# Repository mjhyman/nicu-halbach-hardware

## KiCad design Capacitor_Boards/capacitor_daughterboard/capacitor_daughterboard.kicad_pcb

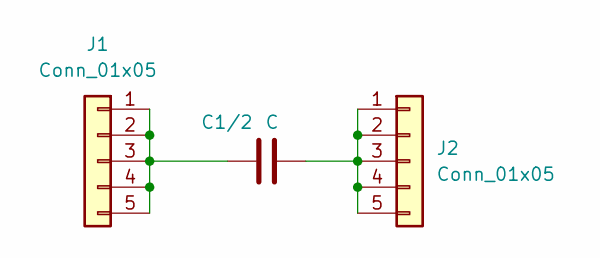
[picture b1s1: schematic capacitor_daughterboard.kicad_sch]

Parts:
C1/2: C; C_2225_5664Metric_Pad1.80x6.60mm_HandSolder
J1, J2: Conn_01x05; PinHeader_1x05_P2.54mm_Vertical

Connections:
unnamed: C1/2.1, J1.1, J1.2, J1.3, J1.4, J1.5
unnamed: C1/2.2, J2.1, J2.2, J2.3, J2.4, J2.5

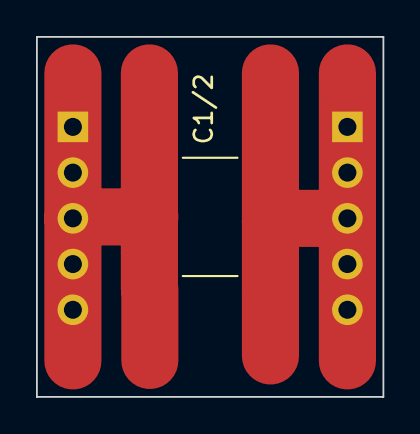
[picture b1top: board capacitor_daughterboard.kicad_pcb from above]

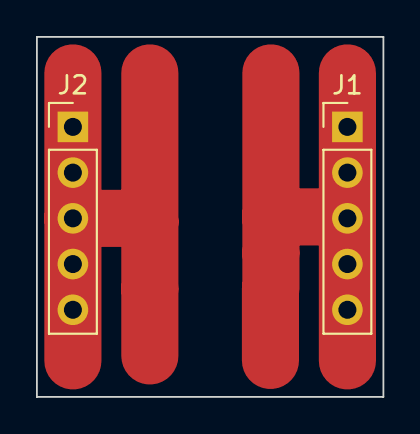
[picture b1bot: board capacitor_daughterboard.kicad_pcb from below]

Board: 2 copper layers, 19.2 x 20.0 mm, 3 parts (2 on the bottom side), 2 nets.

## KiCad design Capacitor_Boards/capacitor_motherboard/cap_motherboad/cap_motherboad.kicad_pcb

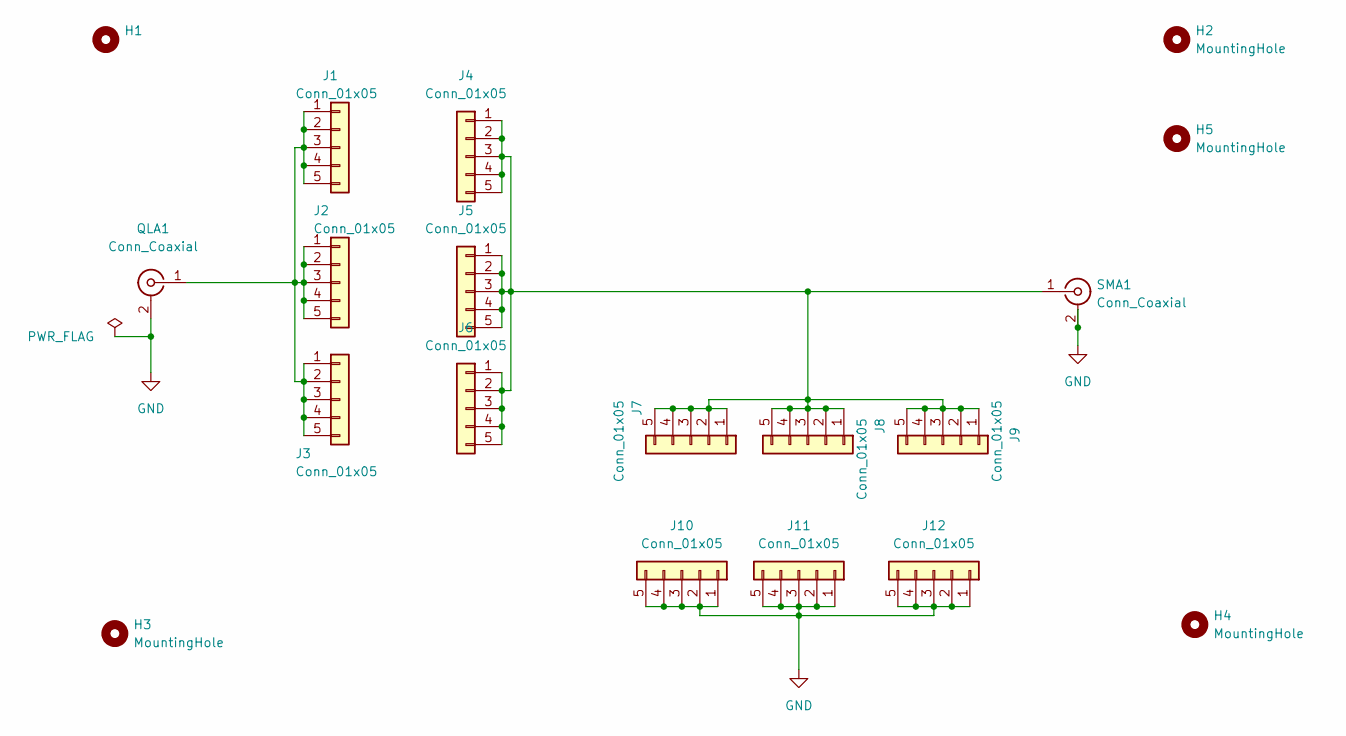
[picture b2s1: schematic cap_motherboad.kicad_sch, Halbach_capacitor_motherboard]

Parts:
H1: (no value)
H2, H3, H4, H5: MountingHole; MountingHole_3.2mm_M3
J1, J2, J3, J4, J5, J6, J7, J8, J9, J10, J11, J12: Conn_01x05; PinSocket_1x05_P2.54mm_Vertical
QLA1: Conn_Coaxial; SMA_Amphenol_132203-12_Horizontal
SMA1: Conn_Coaxial; SMA_Amphenol_132289_EdgeMount

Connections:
GND: J10.1, J10.2, J10.3, J10.4, J10.5, J11.1, J11.2, J11.3, J11.4, J11.5, J12.1, J12.2, J12.3, J12.4, J12.5, QLA1.2 (Ext), SMA1.2 (Ext)
unnamed: J1.1, J1.2, J1.3, J1.4, J1.5, J2.1, J2.2, J2.3, J2.4, J2.5, J3.1, J3.2, J3.3, J3.4, J3.5, QLA1.1 (In)
unnamed: J4.1, J4.2, J4.3, J4.4, J4.5, J5.1, J5.2, J5.3, J5.4, J5.5, J6.1, J6.2, J6.3, J6.4, J6.5, J7.1, J7.2, J7.3, J7.4, J7.5, J8.1, J8.2, J8.3, J8.4, J8.5, J9.1, J9.2, J9.3, J9.4, J9.5, SMA1.1 (In)

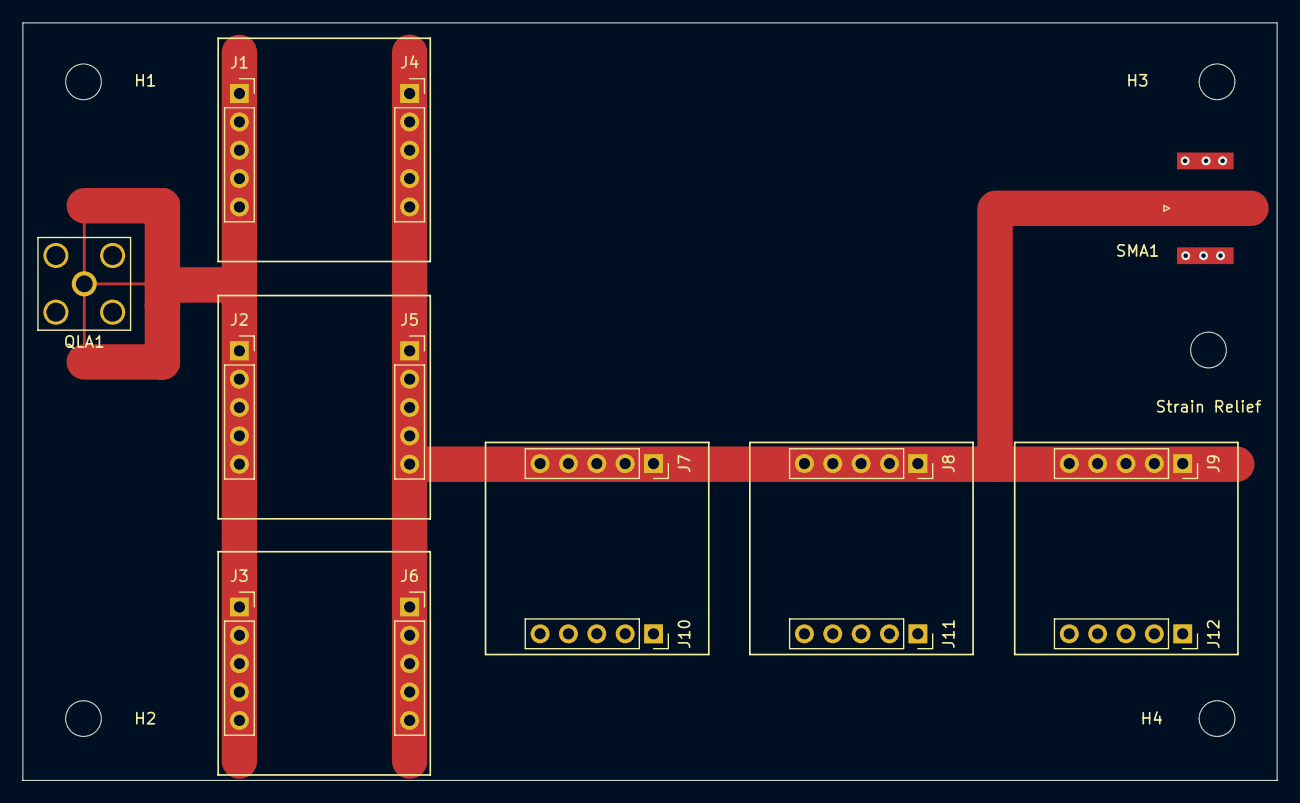
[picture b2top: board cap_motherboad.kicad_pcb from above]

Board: 2 copper layers, 112.4 x 67.9 mm, 19 parts (0 on the bottom side), 3 nets.

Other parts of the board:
Strain Relief: MountingHole; MountingHole_3.2mm_M3

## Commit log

2022-04-22 Adding base design with 3 caps per daughter board
2022-04-22 resized capacitor daughterboard to have just 2 caps.
2022-04-22 Connected the QLA connector
2022-04-22 Revised layout
2022-04-27 Shrunk Daughter Board
2022-04-27 Single pad for caps.
    Further reduced size of daughterboard.
2022-04-29 Finalized boards
